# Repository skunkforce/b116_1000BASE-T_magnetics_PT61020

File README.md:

# edgy_board number b116
This design is part of the [edgy board project](https://github.com/skunkforce/edgy_boards).

# getting started
This repository uses submodules. After cloning use the command 

```$ git submodule update --init --recursive```

to pull the submodules before opening the project with kicad. 

# Tests
Tests can be found in [TESTS.md](TESTS.md)

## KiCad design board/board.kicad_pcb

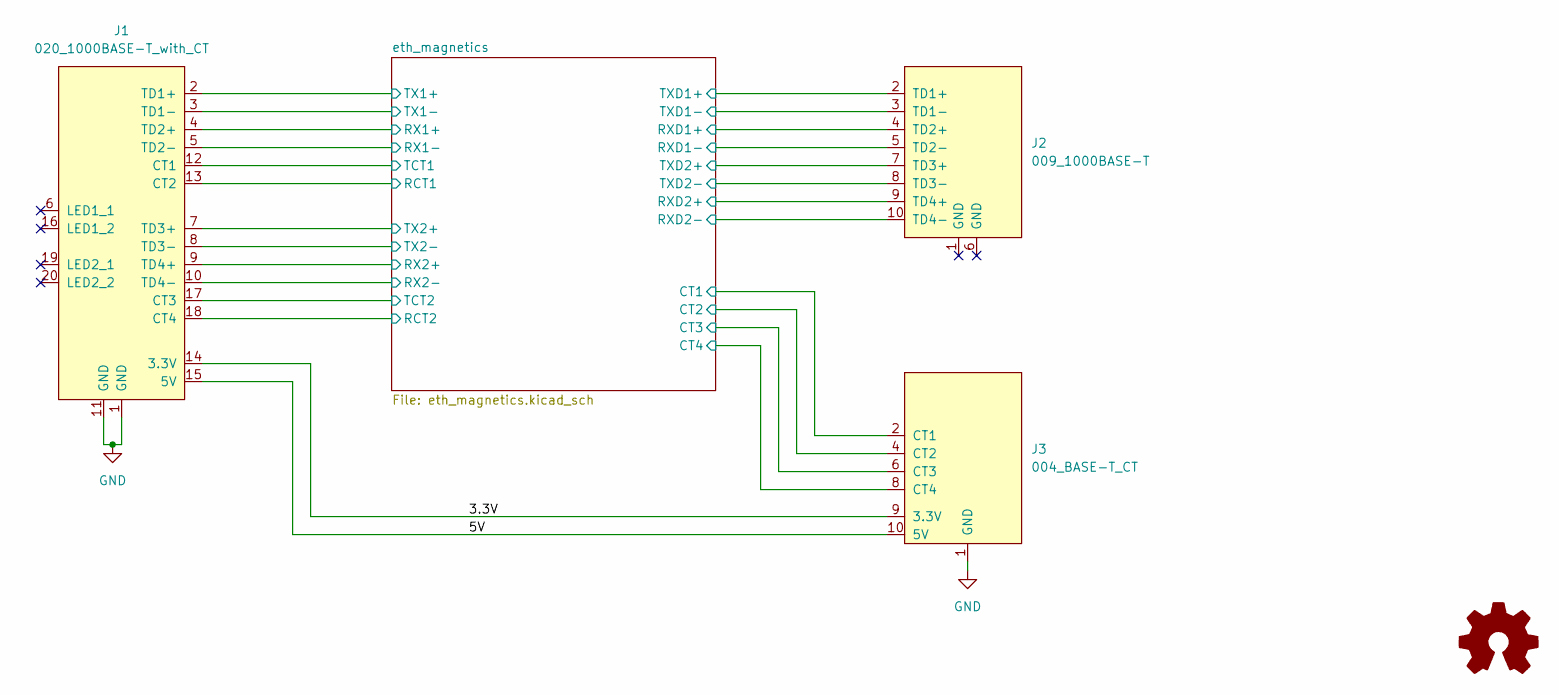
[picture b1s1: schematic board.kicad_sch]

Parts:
J1: 020_1000BASE-T_with_CT; on_edge_2x10_device
J2: 009_1000BASE-T; on_edge_2x05_host
J3: 004_BASE-T_CT; on_edge_2x05_host
LOGO1: Logo_Open_Hardware_Small; OSHW-Symbol_6.7x6mm_SilkScreen

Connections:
/3.3V: J1.14 (3.3V), J3.9 (3.3V)
/5V: J1.15 (5V), J3.10 (5V)
/eth_magnetics/CT1: J3.2 (CT1); also elsewhere on the board
/eth_magnetics/CT2: J3.4 (CT2); also elsewhere on the board
/eth_magnetics/CT3: J3.6 (CT3); also elsewhere on the board
/eth_magnetics/CT4: J3.8 (CT4); also elsewhere on the board
/eth_magnetics/RCT1: J1.13 (CT2); also elsewhere on the board
/eth_magnetics/RCT2: J1.18 (CT4); also elsewhere on the board
/eth_magnetics/RX1+: J1.4 (TD2+); also elsewhere on the board
/eth_magnetics/RX1-: J1.5 (TD2-); also elsewhere on the board
/eth_magnetics/RX2+: J1.9 (TD4+); also elsewhere on the board
/eth_magnetics/RX2-: J1.10 (TD4-); also elsewhere on the board
/eth_magnetics/RXD1+: J2.4 (TD2+); also elsewhere on the board
/eth_magnetics/RXD1-: J2.5 (TD2-); also elsewhere on the board
/eth_magnetics/RXD2+: J2.9 (TD4+); also elsewhere on the board
/eth_magnetics/RXD2-: J2.10 (TD4-); also elsewhere on the board
/eth_magnetics/TCT1: J1.12 (CT1); also elsewhere on the board
/eth_magnetics/TCT2: J1.17 (CT3); also elsewhere on the board
/eth_magnetics/TX1+: J1.2 (TD1+); also elsewhere on the board
/eth_magnetics/TX1-: J1.3 (TD1-); also elsewhere on the board
/eth_magnetics/TX2+: J1.7 (TD3+); also elsewhere on the board
/eth_magnetics/TX2-: J1.8 (TD3-); also elsewhere on the board
/eth_magnetics/TXD1+: J2.2 (TD1+); also elsewhere on the board
/eth_magnetics/TXD1-: J2.3 (TD1-); also elsewhere on the board
/eth_magnetics/TXD2+: J2.7 (TD3+); also elsewhere on the board
/eth_magnetics/TXD2-: J2.8 (TD3-); also elsewhere on the board
GND: J1.1 (GND), J1.11 (GND), J3.1 (GND)

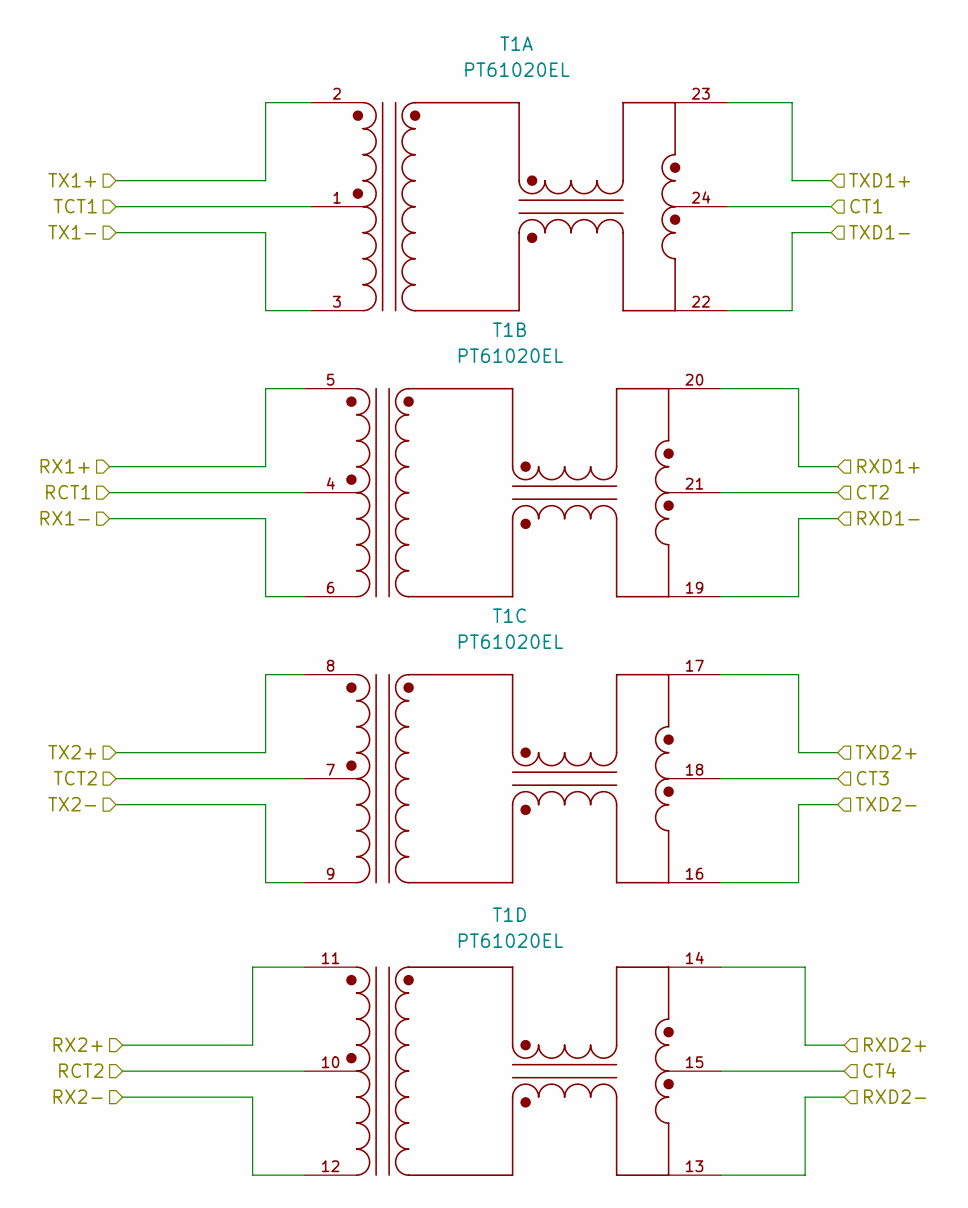
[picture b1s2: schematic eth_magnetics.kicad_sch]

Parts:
T1: PT61020EL; XFMR_PT61020EL; MPN PT61020EL

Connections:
/eth_magnetics/CT1: T1.24; also elsewhere on the board
/eth_magnetics/CT2: T1.21; also elsewhere on the board
/eth_magnetics/CT3: T1.18; also elsewhere on the board
/eth_magnetics/CT4: T1.15; also elsewhere on the board
/eth_magnetics/RCT1: T1.4; also elsewhere on the board
/eth_magnetics/RCT2: T1.10; also elsewhere on the board
/eth_magnetics/RX1+: T1.5; also elsewhere on the board
/eth_magnetics/RX1-: T1.6; also elsewhere on the board
/eth_magnetics/RX2+: T1.11; also elsewhere on the board
/eth_magnetics/RX2-: T1.12; also elsewhere on the board
/eth_magnetics/RXD1+: T1.20; also elsewhere on the board
/eth_magnetics/RXD1-: T1.19; also elsewhere on the board
/eth_magnetics/RXD2+: T1.14; also elsewhere on the board
/eth_magnetics/RXD2-: T1.13; also elsewhere on the board
/eth_magnetics/TCT1: T1.1; also elsewhere on the board
/eth_magnetics/TCT2: T1.7; also elsewhere on the board
/eth_magnetics/TX1+: T1.2; also elsewhere on the board
/eth_magnetics/TX1-: T1.3; also elsewhere on the board
/eth_magnetics/TX2+: T1.8; also elsewhere on the board
/eth_magnetics/TX2-: T1.9; also elsewhere on the board
/eth_magnetics/TXD1+: T1.23; also elsewhere on the board
/eth_magnetics/TXD1-: T1.22; also elsewhere on the board
/eth_magnetics/TXD2+: T1.17; also elsewhere on the board
/eth_magnetics/TXD2-: T1.16; also elsewhere on the board

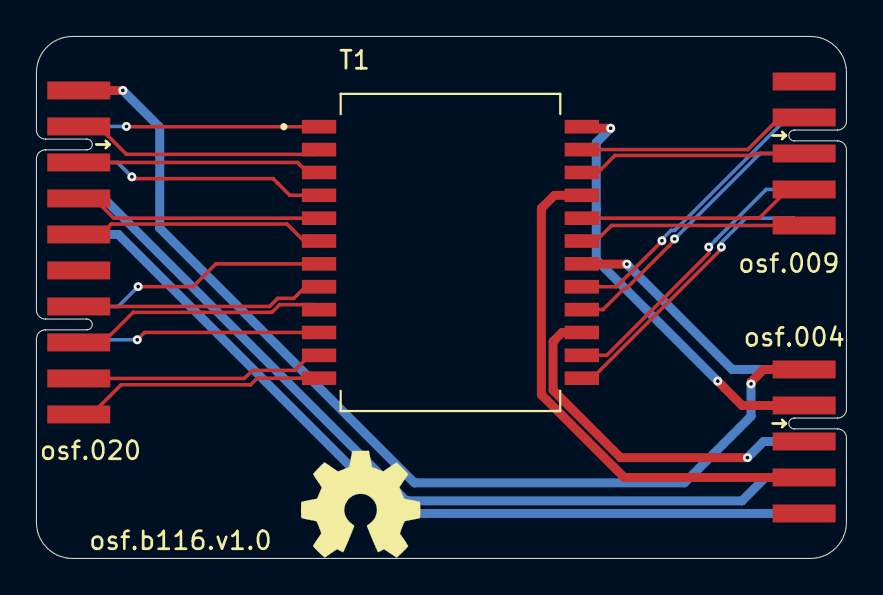
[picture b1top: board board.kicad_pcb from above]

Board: 2 copper layers, 45.0 x 29.0 mm, 5 parts (0 on the bottom side), 27 nets.

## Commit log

2023-03-26 initial
